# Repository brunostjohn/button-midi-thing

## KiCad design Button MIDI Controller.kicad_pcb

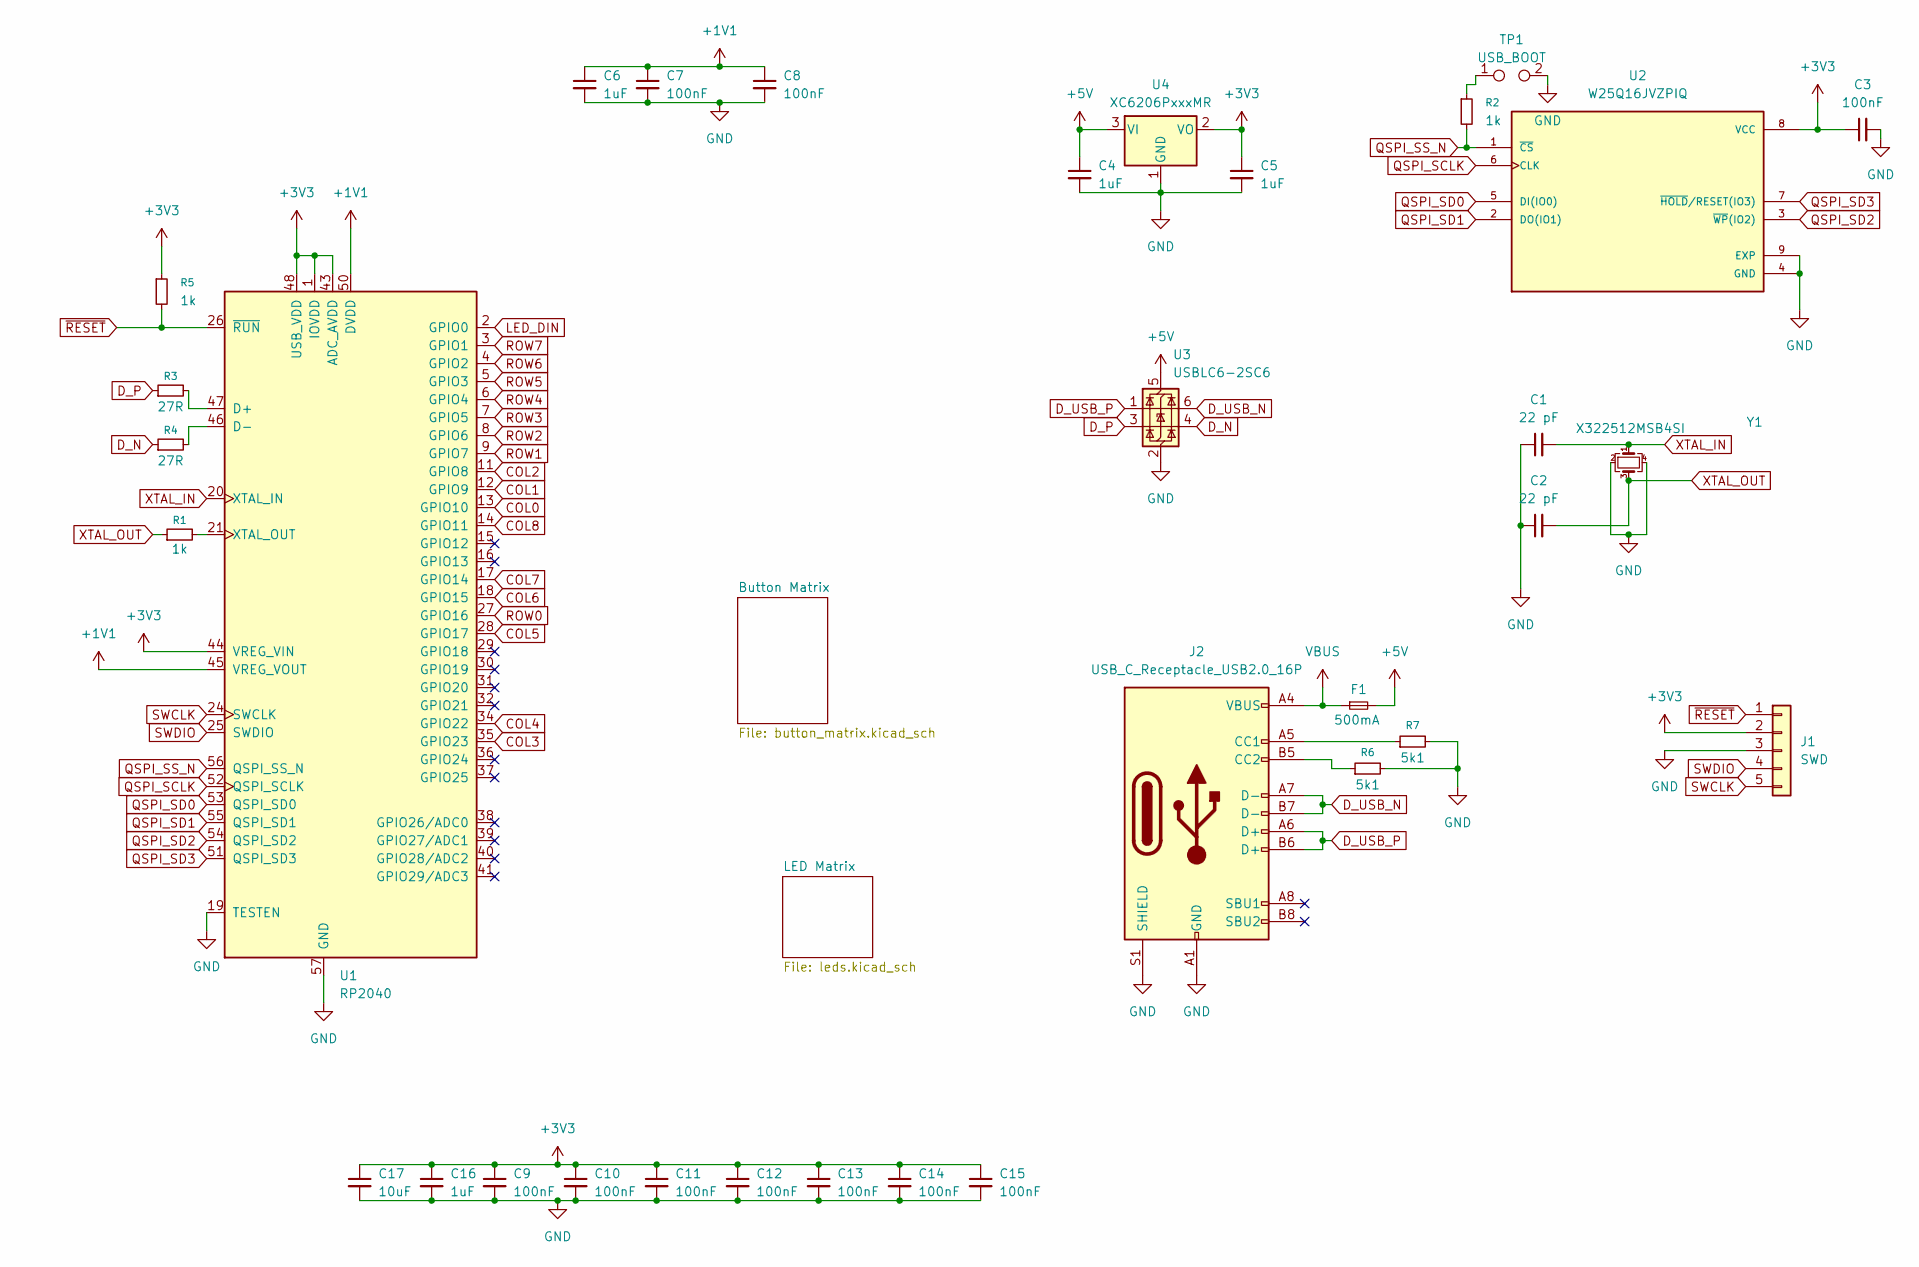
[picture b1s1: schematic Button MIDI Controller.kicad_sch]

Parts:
C1, C2: 22 pF; C_0402_1005Metric-notxt
C3, C7, C8, C9, C10, C11, C12, C13, C14, C15: 100nF; C_0402_1005Metric-notxt
C4, C5, C6, C16: 1uF; C_0402_1005Metric-notxt
C17: 10uF; C_0402_1005Metric-notxt
F1: 500mA; Fuse_0402_1005Metric-notxt
J1: SWD; PinHeader_1x05_P1.00mm_Vertical_SMD_Pin1Right-notxt
J2: USB_C_Receptacle_USB2.0_16P; USB_C_Receptacle_G-Switch_GT-USB-7025-notxt
R1, R2, R5: 1k; R_0402_1005Metric-notext
R3, R4: 27R; R_0402_1005Metric-notext
R6, R7: 5k1; R_0402_1005Metric-notext
TP1: USB_BOOT; TestPoint_Pad_1.0x1.0mm-notxt
U1: RP2040; RP2040-QFN-56-notext
U2: W25Q16JVZPIQ; SON127P500X600X80-9N-notxt
U3: USBLC6-2SC6; SOT-23-6-notxt
U4: XC6206PxxxMR; SOT-23-3-notxt
Y1: X322512MSB4SI; Crystal_SMD_2016-4Pin_2.0x1.6mm-notxt

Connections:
+1V1: C6.1, C7.1, C8.1, U1.23 (DVDD), U1.45 (VREG_VOUT), U1.50 (DVDD)
+3V3: C3.1, C5.1, C9.1, C10.1, C11.1, C12.1, C13.1, C14.1, C15.1, C16.1, C17.1, J1.2, R5.1, U1.1 (IOVDD), U1.10 (IOVDD), U1.22 (IOVDD), U1.33 (IOVDD), U1.42 (IOVDD), U1.43 (ADC_AVDD), U1.44 (VREG_VIN), U1.48 (USB_VDD), U1.49 (IOVDD), U2.8 (VCC), U4.2 (VO)
+5V: C4.1, F1.2, U3.5 (VBUS), U4.3 (VI); also elsewhere on the board
COL0: U1.13 (GPIO10); also elsewhere on the board
COL1: U1.12 (GPIO9); also elsewhere on the board
COL2: U1.11 (GPIO8); also elsewhere on the board
COL3: U1.35 (GPIO23); also elsewhere on the board
COL4: U1.34 (GPIO22); also elsewhere on the board
COL5: U1.28 (GPIO17); also elsewhere on the board
COL6: U1.18 (GPIO15); also elsewhere on the board
COL7: U1.17 (GPIO14); also elsewhere on the board
COL8: U1.14 (GPIO11); also elsewhere on the board
D_N: R4.1, U3.4 (I/O2)
D_P: R3.1, U3.3 (I/O2)
D_USB_N: J2.A7 (D-), J2.B7 (D-), U3.6 (I/O1)
D_USB_P: J2.A6 (D+), J2.B6 (D+), U3.1 (I/O1)
GND: C1.1, C2.1, C3.2, C4.2, C5.2, C6.2, C7.2, C8.2, C9.2, C10.2, C11.2, C12.2, C13.2, C14.2, C15.2, C16.2, C17.2, J1.3, J2.A1 (GND), J2.A12 (GND), J2.B1 (GND), J2.B12 (GND), J2.S1 (SHIELD), R6.2, R7.2, TP1.2, U1.19 (TESTEN), U1.57 (GND), U2.4 (GND), U2.9 (EXP), U3.2 (GND), U4.1 (GND), Y1.2, Y1.4; also elsewhere on the board
LED_DIN: U1.2 (GPIO0); also elsewhere on the board
unnamed: J2.A5 (CC1), R7.1
unnamed: J2.B5 (CC2), R6.1
unnamed: R2.1, TP1.1
unnamed: R3.2, U1.47 (D+)
unnamed: R4.2, U1.46 (D-)
unnamed: R1.2, U1.21 (XTAL_OUT)
QSPI_SCLK: U1.52 (QSPI_SCLK), U2.6 (CLK)
QSPI_SD0: U1.53 (QSPI_SD0), U2.5 (DI(IO0))
QSPI_SD1: U1.55 (QSPI_SD1), U2.2 (DO(IO1))
QSPI_SD2: U1.54 (QSPI_SD2), U2.3 (~WP(IO2))
QSPI_SD3: U1.51 (QSPI_SD3), U2.7 (~HOLD/RESET(IO3))
QSPI_SS_N: R2.2, U1.56 (QSPI_SS_N), U2.1 (~CS)
ROW0: U1.27 (GPIO16); also elsewhere on the board
ROW1: U1.9 (GPIO7); also elsewhere on the board
ROW2: U1.8 (GPIO6); also elsewhere on the board
ROW3: U1.7 (GPIO5); also elsewhere on the board
ROW4: U1.6 (GPIO4); also elsewhere on the board
ROW5: U1.5 (GPIO3); also elsewhere on the board
ROW6: U1.4 (GPIO2); also elsewhere on the board
ROW7: U1.3 (GPIO1); also elsewhere on the board
SWCLK: J1.5, U1.24 (SWCLK)
SWDIO: J1.4, U1.25 (SWDIO)
VBUS: F1.1, J2.A4 (VBUS), J2.A9 (VBUS), J2.B4 (VBUS), J2.B9 (VBUS)
XTAL_IN: C1.2, U1.20 (XTAL_IN), Y1.1
XTAL_OUT: C2.2, R1.1, Y1.3
~RESET: J1.1, R5.2, U1.26 (~RUN)

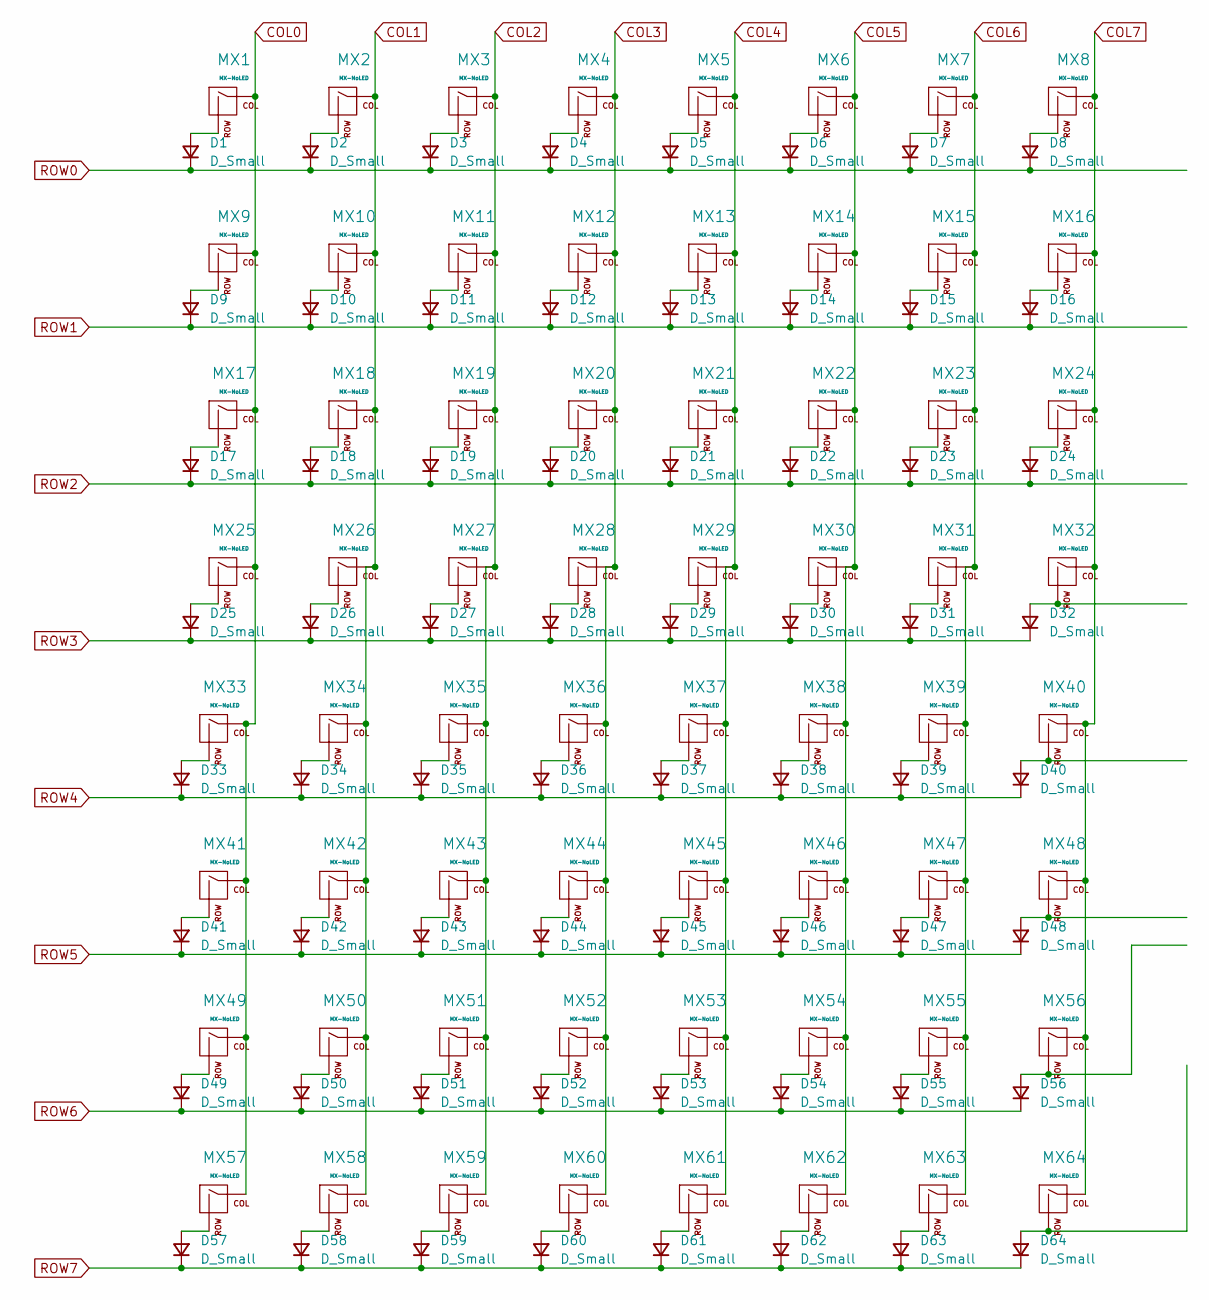
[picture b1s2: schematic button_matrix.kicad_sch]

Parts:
D1, D2, D3, D4, D5, D6, D7, D8, D9, D10, D11, D12, D13, D14, D15, D16, D17, D18, D19, D20, D21, D22, D23, D24, D25, D26, D27, D28, D29, D30, D31, D32, D33, D34, D35, D36, D37, D38, D39, D40, D41, D42, D43, D44, D45, D46, D47, D48, D49, D50, D51, D52, D53, D54, D55, D56, D57, D58, D59, D60, D61, D62, D63, D64: D_Small; D_0603_1608Metric_NOTXTNOTFUCKD
MX1, MX2, MX3, MX4, MX5, MX6, MX7, MX8, MX9, MX10, MX11, MX12, MX13, MX14, MX15, MX16, MX17, MX18, MX19, MX20, MX21, MX22, MX23, MX24, MX25, MX26, MX27, MX28, MX29, MX30, MX31, MX32, MX33, MX34, MX35, MX36, MX37, MX38, MX39, MX40, MX41, MX42, MX43, MX44, MX45, MX46, MX47, MX48, MX49, MX50, MX51, MX52, MX53, MX54, MX55, MX56, MX57, MX58, MX59, MX60, MX61, MX62, MX63, MX64: MX-NoLED; OBSC-30 SW-68

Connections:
COL0: MX1.1 (COL), MX9.1 (COL), MX17.1 (COL), MX25.1 (COL), MX33.1 (COL), MX41.1 (COL), MX49.1 (COL), MX57.1 (COL); also elsewhere on the board
COL1: MX2.1 (COL), MX10.1 (COL), MX18.1 (COL), MX26.1 (COL), MX34.1 (COL), MX42.1 (COL), MX50.1 (COL), MX58.1 (COL); also elsewhere on the board
COL2: MX3.1 (COL), MX11.1 (COL), MX19.1 (COL), MX27.1 (COL), MX35.1 (COL), MX43.1 (COL), MX51.1 (COL), MX59.1 (COL); also elsewhere on the board
COL3: MX4.1 (COL), MX12.1 (COL), MX20.1 (COL), MX28.1 (COL), MX36.1 (COL), MX44.1 (COL), MX52.1 (COL), MX60.1 (COL); also elsewhere on the board
COL4: MX5.1 (COL), MX13.1 (COL), MX21.1 (COL), MX29.1 (COL), MX37.1 (COL), MX45.1 (COL), MX53.1 (COL), MX61.1 (COL); also elsewhere on the board
COL5: MX6.1 (COL), MX14.1 (COL), MX22.1 (COL), MX30.1 (COL), MX38.1 (COL), MX46.1 (COL), MX54.1 (COL), MX62.1 (COL); also elsewhere on the board
COL6: MX7.1 (COL), MX15.1 (COL), MX23.1 (COL), MX31.1 (COL), MX39.1 (COL), MX47.1 (COL), MX55.1 (COL), MX63.1 (COL); also elsewhere on the board
COL7: MX8.1 (COL), MX16.1 (COL), MX24.1 (COL), MX32.1 (COL), MX40.1 (COL), MX48.1 (COL), MX56.1 (COL), MX64.1 (COL); also elsewhere on the board
unnamed: D1.2 (A), MX1.2 (ROW)
unnamed: D2.2 (A), MX2.2 (ROW)
unnamed: D3.2 (A), MX3.2 (ROW)
unnamed: D4.2 (A), MX4.2 (ROW)
unnamed: D5.2 (A), MX5.2 (ROW)
unnamed: D6.2 (A), MX6.2 (ROW)
unnamed: D7.2 (A), MX7.2 (ROW)
unnamed: D8.2 (A), MX8.2 (ROW)
unnamed: D9.2 (A), MX9.2 (ROW)
unnamed: D10.2 (A), MX10.2 (ROW)
unnamed: D11.2 (A), MX11.2 (ROW)
unnamed: D12.2 (A), MX12.2 (ROW)
unnamed: D13.2 (A), MX13.2 (ROW)
unnamed: D14.2 (A), MX14.2 (ROW)
unnamed: D15.2 (A), MX15.2 (ROW)
unnamed: D16.2 (A), MX16.2 (ROW)
unnamed: D17.2 (A), MX17.2 (ROW)
unnamed: D18.2 (A), MX18.2 (ROW)
unnamed: D19.2 (A), MX19.2 (ROW)
unnamed: D20.2 (A), MX20.2 (ROW)
unnamed: D21.2 (A), MX21.2 (ROW)
unnamed: D22.2 (A), MX22.2 (ROW)
unnamed: D23.2 (A), MX23.2 (ROW)
unnamed: D24.2 (A), MX24.2 (ROW)
unnamed: D25.2 (A), MX25.2 (ROW)
unnamed: D26.2 (A), MX26.2 (ROW)
unnamed: D27.2 (A), MX27.2 (ROW)
unnamed: D28.2 (A), MX28.2 (ROW)
unnamed: D29.2 (A), MX29.2 (ROW)
unnamed: D30.2 (A), MX30.2 (ROW)
unnamed: D31.2 (A), MX31.2 (ROW)
unnamed: D32.2 (A), MX32.2 (ROW)
unnamed: D33.2 (A), MX33.2 (ROW)
unnamed: D34.2 (A), MX34.2 (ROW)
unnamed: D35.2 (A), MX35.2 (ROW)
unnamed: D36.2 (A), MX36.2 (ROW)
unnamed: D37.2 (A), MX37.2 (ROW)
unnamed: D38.2 (A), MX38.2 (ROW)
unnamed: D39.2 (A), MX39.2 (ROW)
unnamed: D40.2 (A), MX40.2 (ROW)
unnamed: D41.2 (A), MX41.2 (ROW)
unnamed: D42.2 (A), MX42.2 (ROW)
unnamed: D43.2 (A), MX43.2 (ROW)
unnamed: D44.2 (A), MX44.2 (ROW)
unnamed: D45.2 (A), MX45.2 (ROW)
unnamed: D46.2 (A), MX46.2 (ROW)
unnamed: D47.2 (A), MX47.2 (ROW)
unnamed: D48.2 (A), MX48.2 (ROW)
unnamed: D49.2 (A), MX49.2 (ROW)
unnamed: D50.2 (A), MX50.2 (ROW)
unnamed: D51.2 (A), MX51.2 (ROW)
unnamed: D52.2 (A), MX52.2 (ROW)
unnamed: D53.2 (A), MX53.2 (ROW)
unnamed: D54.2 (A), MX54.2 (ROW)
unnamed: D55.2 (A), MX55.2 (ROW)
unnamed: D56.2 (A), MX56.2 (ROW)
unnamed: D57.2 (A), MX57.2 (ROW)
unnamed: D58.2 (A), MX58.2 (ROW)
unnamed: D59.2 (A), MX59.2 (ROW)
unnamed: D60.2 (A), MX60.2 (ROW)
unnamed: D61.2 (A), MX61.2 (ROW)
unnamed: D62.2 (A), MX62.2 (ROW)
unnamed: D63.2 (A), MX63.2 (ROW)
unnamed: D64.2 (A), MX64.2 (ROW)
ROW0: D1.1 (K), D2.1 (K), D3.1 (K), D4.1 (K), D5.1 (K), D6.1 (K), D7.1 (K), D8.1 (K); also elsewhere on the board
ROW1: D9.1 (K), D10.1 (K), D11.1 (K), D12.1 (K), D13.1 (K), D14.1 (K), D15.1 (K), D16.1 (K); also elsewhere on the board
ROW2: D17.1 (K), D18.1 (K), D19.1 (K), D20.1 (K), D21.1 (K), D22.1 (K), D23.1 (K), D24.1 (K); also elsewhere on the board
ROW3: D25.1 (K), D26.1 (K), D27.1 (K), D28.1 (K), D29.1 (K), D30.1 (K), D31.1 (K), D32.1 (K); also elsewhere on the board
ROW4: D33.1 (K), D34.1 (K), D35.1 (K), D36.1 (K), D37.1 (K), D38.1 (K), D39.1 (K), D40.1 (K); also elsewhere on the board
ROW5: D41.1 (K), D42.1 (K), D43.1 (K), D44.1 (K), D45.1 (K), D46.1 (K), D47.1 (K), D48.1 (K); also elsewhere on the board
ROW6: D49.1 (K), D50.1 (K), D51.1 (K), D52.1 (K), D53.1 (K), D54.1 (K), D55.1 (K), D56.1 (K); also elsewhere on the board
ROW7: D57.1 (K), D58.1 (K), D59.1 (K), D60.1 (K), D61.1 (K), D62.1 (K), D63.1 (K), D64.1 (K); also elsewhere on the board

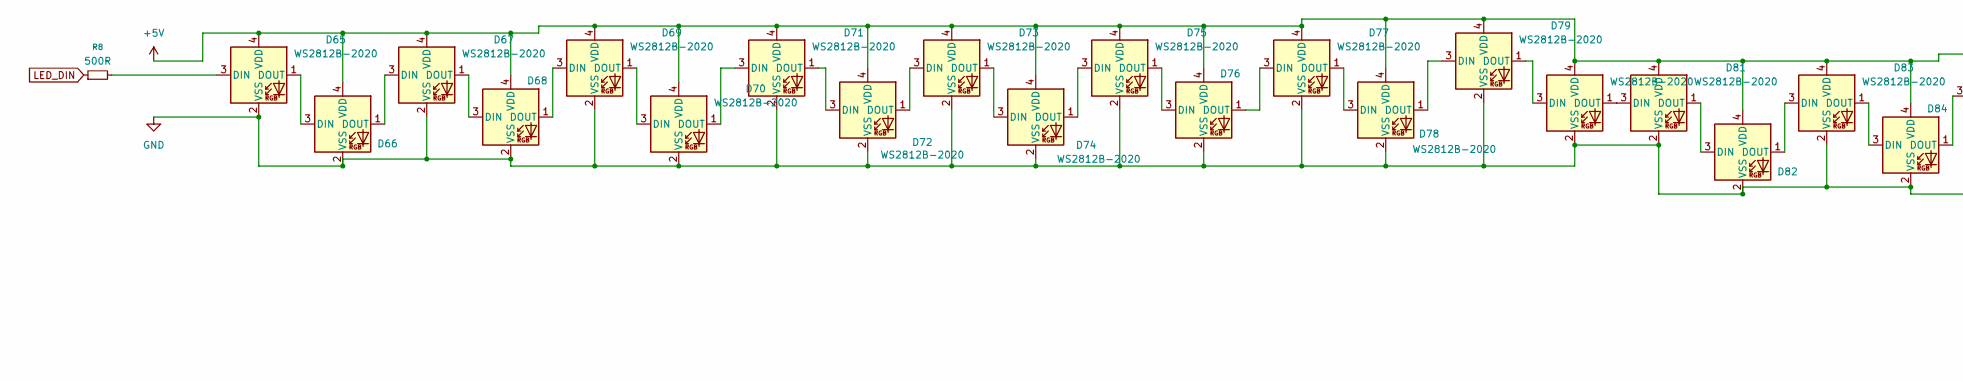
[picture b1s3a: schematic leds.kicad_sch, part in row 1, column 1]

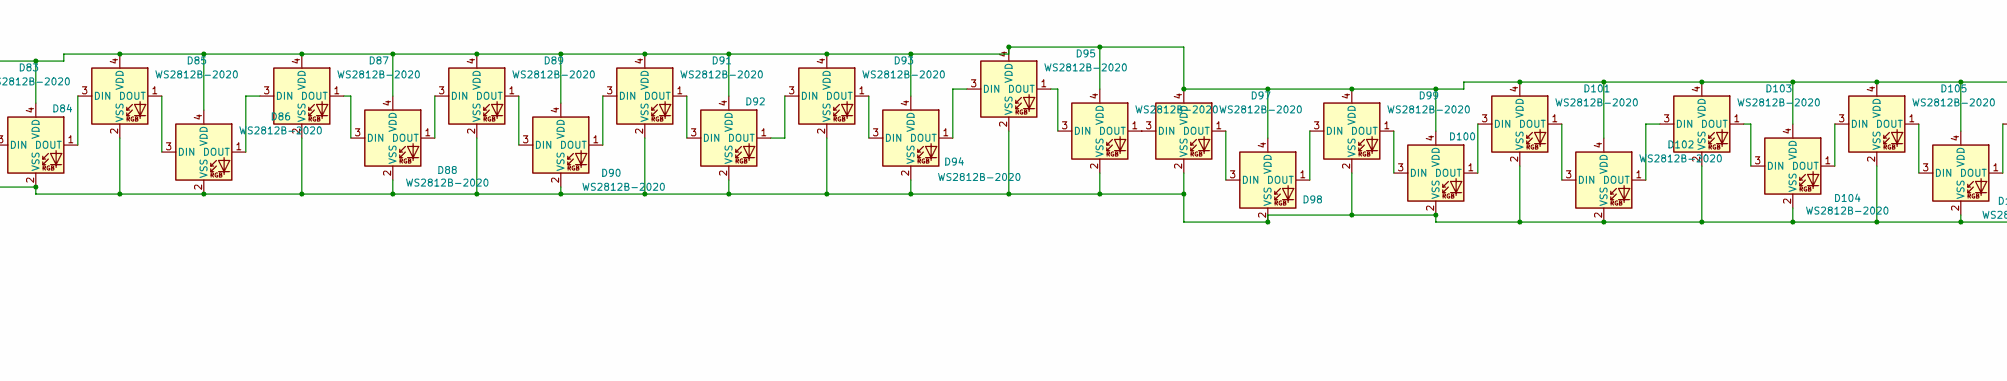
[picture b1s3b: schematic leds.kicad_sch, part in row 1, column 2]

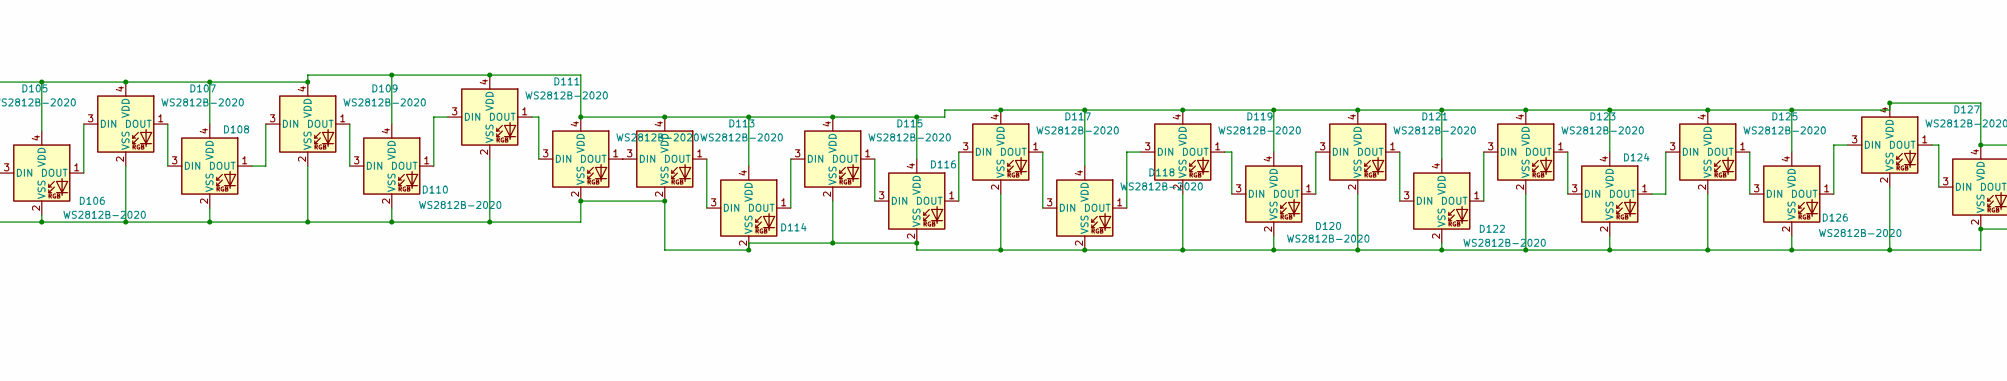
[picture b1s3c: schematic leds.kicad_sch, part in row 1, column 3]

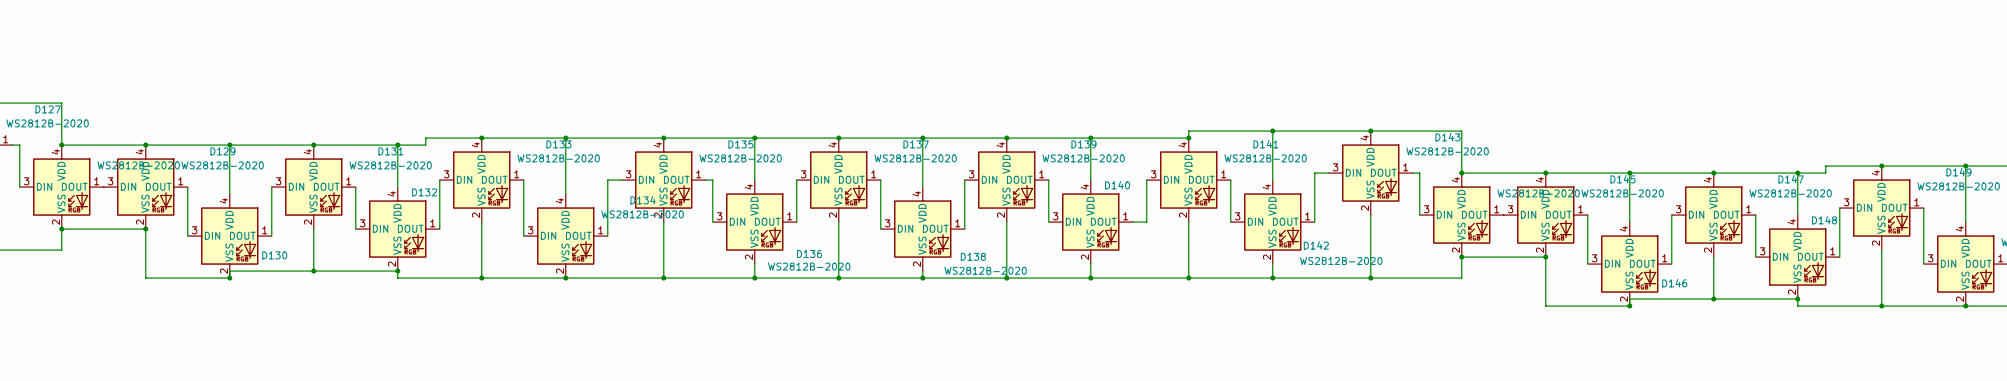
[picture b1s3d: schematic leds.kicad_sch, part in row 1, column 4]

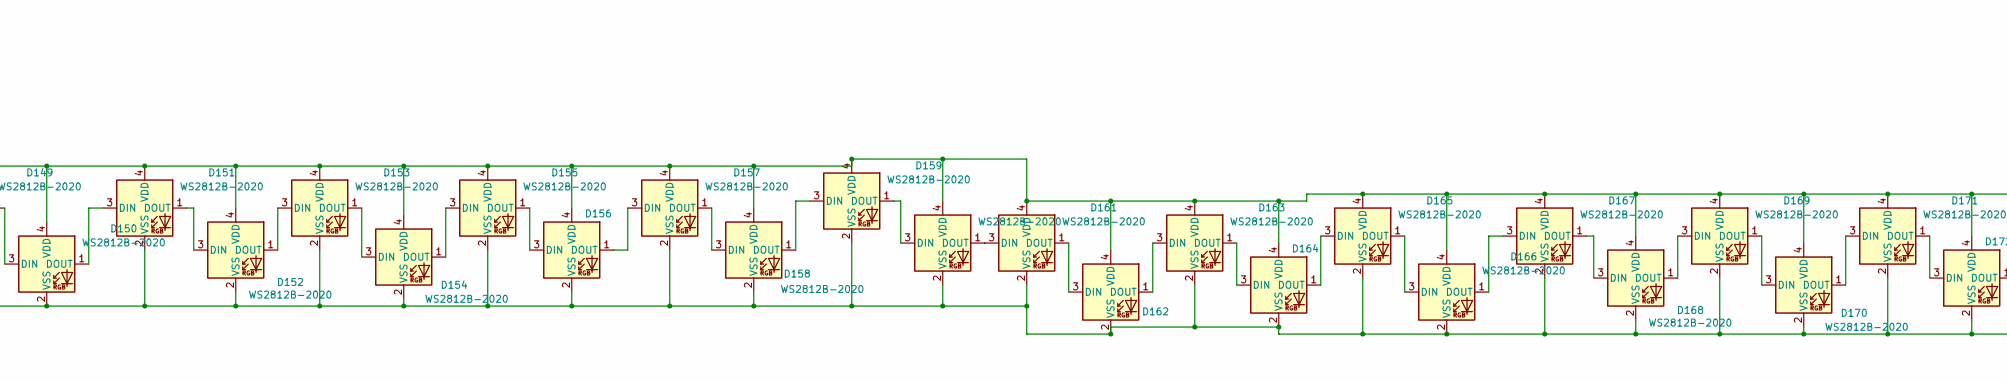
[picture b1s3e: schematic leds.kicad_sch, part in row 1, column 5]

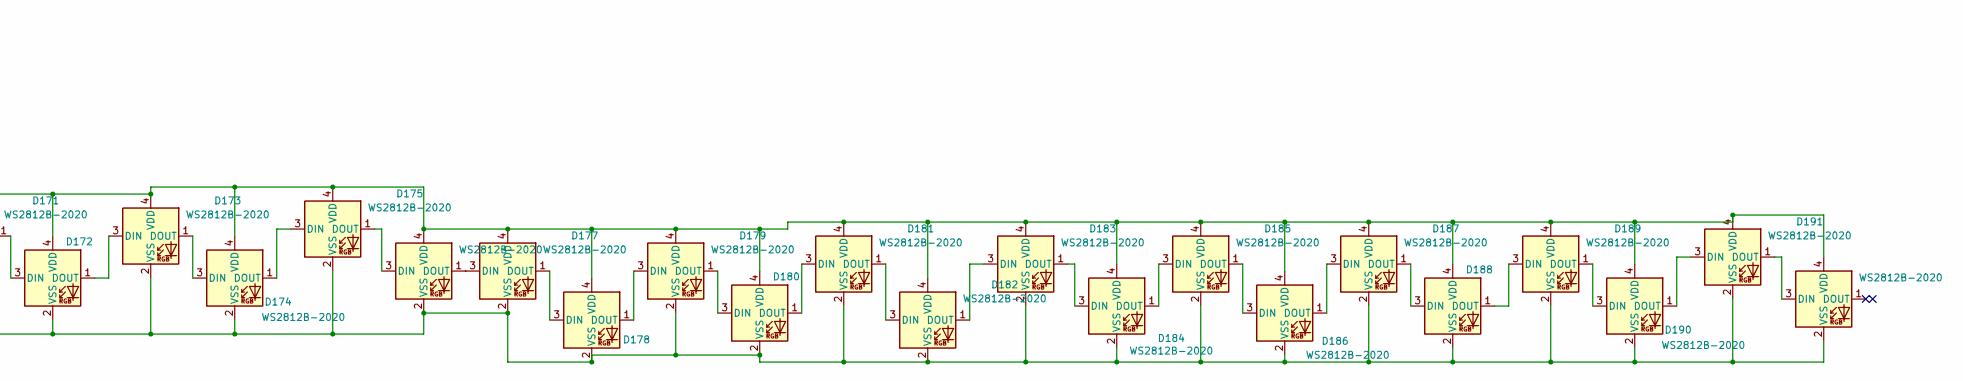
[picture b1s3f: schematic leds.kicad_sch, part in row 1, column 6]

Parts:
D65, D66, D67, D68, D69, D70, D71, D72, D73, D74, D75, D76, D77, D78, D79, D80, D81, D82, D83, D84, D85, D86, D87, D88, D89, D90, D91, D92, D93, D94, D95, D96, D97, D98, D99, D100, D101, D102, D103, D104, D105, D106, D107, D108, D109, D110, D111, D112, D113, D114, D115, D116, D117, D118, D119, D120, D121, D122, D123, D124, D125, D126, D127, D128, D129, D130, D131, D132, D133, D134, D135, D136, D137, D138, D139, D140, D141, D142, D143, D144, D145, D146, D147, D148, D149, D150, D151, D152, D153, D154, D155, D156, D157, D158, D159, D160, D161, D162, D163, D164, D165, D166, D167, D168, D169, D170, D171, D172, D173, D174, D175, D176, D177, D178, D179, D180, D181, D182, D183, D184, D185, D186, D187, D188, D189, D190, D191, D192: WS2812B-2020; LED_WS2812B-2020_PLCC4_2.0x2.0mm-notext
R8: 500R; R_0402_1005Metric-notext

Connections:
+5V: D65.4 (VDD), D66.4 (VDD), D67.4 (VDD), D68.4 (VDD), D69.4 (VDD), D70.4 (VDD), D71.4 (VDD), D72.4 (VDD), D73.4 (VDD), D74.4 (VDD), D75.4 (VDD), D76.4 (VDD), D77.4 (VDD), D78.4 (VDD), D79.4 (VDD), D80.4 (VDD), D81.4 (VDD), D82.4 (VDD), D83.4 (VDD), D84.4 (VDD), D85.4 (VDD), D86.4 (VDD), D87.4 (VDD), D88.4 (VDD), D89.4 (VDD), D90.4 (VDD), D91.4 (VDD), D92.4 (VDD), D93.4 (VDD), D94.4 (VDD), D95.4 (VDD), D96.4 (VDD), D97.4 (VDD), D98.4 (VDD), D99.4 (VDD), D100.4 (VDD), D101.4 (VDD), D102.4 (VDD), D103.4 (VDD), D104.4 (VDD), D105.4 (VDD), D106.4 (VDD), D107.4 (VDD), D108.4 (VDD), D109.4 (VDD), D110.4 (VDD), D111.4 (VDD), D112.4 (VDD), D113.4 (VDD), D114.4 (VDD), D115.4 (VDD), D116.4 (VDD), D117.4 (VDD), D118.4 (VDD), D119.4 (VDD), D120.4 (VDD), D121.4 (VDD), D122.4 (VDD), D123.4 (VDD), D124.4 (VDD), D125.4 (VDD), D126.4 (VDD), D127.4 (VDD), D128.4 (VDD), D129.4 (VDD), D130.4 (VDD), D131.4 (VDD), D132.4 (VDD), D133.4 (VDD), D134.4 (VDD), D135.4 (VDD), D136.4 (VDD), D137.4 (VDD), D138.4 (VDD), D139.4 (VDD), D140.4 (VDD), D141.4 (VDD), D142.4 (VDD), D143.4 (VDD), D144.4 (VDD), D145.4 (VDD), D146.4 (VDD), D147.4 (VDD), D148.4 (VDD), D149.4 (VDD), D150.4 (VDD), D151.4 (VDD), D152.4 (VDD), D153.4 (VDD), D154.4 (VDD), D155.4 (VDD), D156.4 (VDD), D157.4 (VDD), D158.4 (VDD), D159.4 (VDD), D160.4 (VDD), D161.4 (VDD), D162.4 (VDD), D163.4 (VDD), D164.4 (VDD), D165.4 (VDD), D166.4 (VDD), D167.4 (VDD), D168.4 (VDD), D169.4 (VDD), D170.4 (VDD), D171.4 (VDD), D172.4 (VDD), D173.4 (VDD), D174.4 (VDD), D175.4 (VDD), D176.4 (VDD), D177.4 (VDD), D178.4 (VDD), D179.4 (VDD), D180.4 (VDD), D181.4 (VDD), D182.4 (VDD), D183.4 (VDD), D184.4 (VDD), D185.4 (VDD), D186.4 (VDD), D187.4 (VDD), D188.4 (VDD), D189.4 (VDD), D190.4 (VDD), D191.4 (VDD), D192.4 (VDD); also elsewhere on the board
GND: D65.2 (VSS), D66.2 (VSS), D67.2 (VSS), D68.2 (VSS), D69.2 (VSS), D70.2 (VSS), D71.2 (VSS), D72.2 (VSS), D73.2 (VSS), D74.2 (VSS), D75.2 (VSS), D76.2 (VSS), D77.2 (VSS), D78.2 (VSS), D79.2 (VSS), D80.2 (VSS), D81.2 (VSS), D82.2 (VSS), D83.2 (VSS), D84.2 (VSS), D85.2 (VSS), D86.2 (VSS), D87.2 (VSS), D88.2 (VSS), D89.2 (VSS), D90.2 (VSS), D91.2 (VSS), D92.2 (VSS), D93.2 (VSS), D94.2 (VSS), D95.2 (VSS), D96.2 (VSS), D97.2 (VSS), D98.2 (VSS), D99.2 (VSS), D100.2 (VSS), D101.2 (VSS), D102.2 (VSS), D103.2 (VSS), D104.2 (VSS), D105.2 (VSS), D106.2 (VSS), D107.2 (VSS), D108.2 (VSS), D109.2 (VSS), D110.2 (VSS), D111.2 (VSS), D112.2 (VSS), D113.2 (VSS), D114.2 (VSS), D115.2 (VSS), D116.2 (VSS), D117.2 (VSS), D118.2 (VSS), D119.2 (VSS), D120.2 (VSS), D121.2 (VSS), D122.2 (VSS), D123.2 (VSS), D124.2 (VSS), D125.2 (VSS), D126.2 (VSS), D127.2 (VSS), D128.2 (VSS), D129.2 (VSS), D130.2 (VSS), D131.2 (VSS), D132.2 (VSS), D133.2 (VSS), D134.2 (VSS), D135.2 (VSS), D136.2 (VSS), D137.2 (VSS), D138.2 (VSS), D139.2 (VSS), D140.2 (VSS), D141.2 (VSS), D142.2 (VSS), D143.2 (VSS), D144.2 (VSS), D145.2 (VSS), D146.2 (VSS), D147.2 (VSS), D148.2 (VSS), D149.2 (VSS), D150.2 (VSS), D151.2 (VSS), D152.2 (VSS), D153.2 (VSS), D154.2 (VSS), D155.2 (VSS), D156.2 (VSS), D157.2 (VSS), D158.2 (VSS), D159.2 (VSS), D160.2 (VSS), D161.2 (VSS), D162.2 (VSS), D163.2 (VSS), D164.2 (VSS), D165.2 (VSS), D166.2 (VSS), D167.2 (VSS), D168.2 (VSS), D169.2 (VSS), D170.2 (VSS), D171.2 (VSS), D172.2 (VSS), D173.2 (VSS), D174.2 (VSS), D175.2 (VSS), D176.2 (VSS), D177.2 (VSS), D178.2 (VSS), D179.2 (VSS), D180.2 (VSS), D181.2 (VSS), D182.2 (VSS), D183.2 (VSS), D184.2 (VSS), D185.2 (VSS), D186.2 (VSS), D187.2 (VSS), D188.2 (VSS), D189.2 (VSS), D190.2 (VSS), D191.2 (VSS), D192.2 (VSS); also elsewhere on the board
LED_DIN: R8.1; also elsewhere on the board
unnamed: D65.3 (DIN), R8.2
unnamed: D65.1 (DOUT), D66.3 (DIN)
unnamed: D66.1 (DOUT), D67.3 (DIN)
unnamed: D67.1 (DOUT), D68.3 (DIN)
unnamed: D68.1 (DOUT), D69.3 (DIN)
unnamed: D69.1 (DOUT), D70.3 (DIN)
unnamed: D70.1 (DOUT), D71.3 (DIN)
unnamed: D71.1 (DOUT), D72.3 (DIN)
unnamed: D72.1 (DOUT), D73.3 (DIN)
unnamed: D73.1 (DOUT), D74.3 (DIN)
unnamed: D74.1 (DOUT), D75.3 (DIN)
unnamed: D75.1 (DOUT), D76.3 (DIN)
unnamed: D76.1 (DOUT), D77.3 (DIN)
unnamed: D77.1 (DOUT), D78.3 (DIN)
unnamed: D78.1 (DOUT), D79.3 (DIN)
unnamed: D79.1 (DOUT), D80.3 (DIN)
unnamed: D80.1 (DOUT), D81.3 (DIN)
unnamed: D81.1 (DOUT), D82.3 (DIN)
unnamed: D82.1 (DOUT), D83.3 (DIN)
unnamed: D83.1 (DOUT), D84.3 (DIN)
unnamed: D84.1 (DOUT), D85.3 (DIN)
unnamed: D85.1 (DOUT), D86.3 (DIN)
unnamed: D86.1 (DOUT), D87.3 (DIN)
unnamed: D87.1 (DOUT), D88.3 (DIN)
unnamed: D88.1 (DOUT), D89.3 (DIN)
unnamed: D89.1 (DOUT), D90.3 (DIN)
unnamed: D90.1 (DOUT), D91.3 (DIN)
unnamed: D91.1 (DOUT), D92.3 (DIN)
unnamed: D92.1 (DOUT), D93.3 (DIN)
unnamed: D93.1 (DOUT), D94.3 (DIN)
unnamed: D94.1 (DOUT), D95.3 (DIN)
unnamed: D95.1 (DOUT), D96.3 (DIN)
unnamed: D96.1 (DOUT), D97.3 (DIN)
unnamed: D97.1 (DOUT), D98.3 (DIN)
unnamed: D98.1 (DOUT), D99.3 (DIN)
unnamed: D99.1 (DOUT), D100.3 (DIN)
unnamed: D100.1 (DOUT), D101.3 (DIN)
unnamed: D101.1 (DOUT), D102.3 (DIN)
unnamed: D102.1 (DOUT), D103.3 (DIN)
unnamed: D103.1 (DOUT), D104.3 (DIN)
unnamed: D104.1 (DOUT), D105.3 (DIN)
unnamed: D105.1 (DOUT), D106.3 (DIN)
unnamed: D106.1 (DOUT), D107.3 (DIN)
unnamed: D107.1 (DOUT), D108.3 (DIN)
unnamed: D108.1 (DOUT), D109.3 (DIN)
unnamed: D109.1 (DOUT), D110.3 (DIN)
unnamed: D110.1 (DOUT), D111.3 (DIN)
unnamed: D111.1 (DOUT), D112.3 (DIN)
unnamed: D112.1 (DOUT), D113.3 (DIN)
unnamed: D113.1 (DOUT), D114.3 (DIN)
unnamed: D114.1 (DOUT), D115.3 (DIN)
unnamed: D115.1 (DOUT), D116.3 (DIN)
unnamed: D116.1 (DOUT), D117.3 (DIN)
unnamed: D117.1 (DOUT), D118.3 (DIN)
unnamed: D118.1 (DOUT), D119.3 (DIN)
unnamed: D119.1 (DOUT), D120.3 (DIN)
unnamed: D120.1 (DOUT), D121.3 (DIN)
unnamed: D121.1 (DOUT), D122.3 (DIN)
unnamed: D122.1 (DOUT), D123.3 (DIN)
unnamed: D123.1 (DOUT), D124.3 (DIN)
unnamed: D124.1 (DOUT), D125.3 (DIN)
unnamed: D125.1 (DOUT), D126.3 (DIN)
unnamed: D126.1 (DOUT), D127.3 (DIN)
unnamed: D127.1 (DOUT), D128.3 (DIN)
unnamed: D128.1 (DOUT), D129.3 (DIN)
unnamed: D129.1 (DOUT), D130.3 (DIN)
unnamed: D130.1 (DOUT), D131.3 (DIN)
unnamed: D131.1 (DOUT), D132.3 (DIN)
unnamed: D132.1 (DOUT), D133.3 (DIN)
unnamed: D133.1 (DOUT), D134.3 (DIN)
unnamed: D134.1 (DOUT), D135.3 (DIN)
unnamed: D135.1 (DOUT), D136.3 (DIN)
unnamed: D136.1 (DOUT), D137.3 (DIN)
unnamed: D137.1 (DOUT), D138.3 (DIN)
unnamed: D138.1 (DOUT), D139.3 (DIN)
unnamed: D139.1 (DOUT), D140.3 (DIN)
unnamed: D140.1 (DOUT), D141.3 (DIN)
unnamed: D141.1 (DOUT), D142.3 (DIN)
unnamed: D142.1 (DOUT), D143.3 (DIN)
unnamed: D143.1 (DOUT), D144.3 (DIN)
unnamed: D144.1 (DOUT), D145.3 (DIN)
unnamed: D145.1 (DOUT), D146.3 (DIN)
unnamed: D146.1 (DOUT), D147.3 (DIN)
unnamed: D147.1 (DOUT), D148.3 (DIN)
unnamed: D148.1 (DOUT), D149.3 (DIN)
unnamed: D149.1 (DOUT), D150.3 (DIN)
unnamed: D150.1 (DOUT), D151.3 (DIN)
unnamed: D151.1 (DOUT), D152.3 (DIN)
unnamed: D152.1 (DOUT), D153.3 (DIN)
unnamed: D153.1 (DOUT), D154.3 (DIN)
unnamed: D154.1 (DOUT), D155.3 (DIN)
unnamed: D155.1 (DOUT), D156.3 (DIN)
unnamed: D156.1 (DOUT), D157.3 (DIN)
unnamed: D157.1 (DOUT), D158.3 (DIN)
unnamed: D158.1 (DOUT), D159.3 (DIN)
unnamed: D159.1 (DOUT), D160.3 (DIN)
unnamed: D160.1 (DOUT), D161.3 (DIN)
unnamed: D161.1 (DOUT), D162.3 (DIN)
unnamed: D162.1 (DOUT), D163.3 (DIN)
unnamed: D163.1 (DOUT), D164.3 (DIN)
unnamed: D164.1 (DOUT), D165.3 (DIN)
unnamed: D165.1 (DOUT), D166.3 (DIN)
unnamed: D166.1 (DOUT), D167.3 (DIN)
unnamed: D167.1 (DOUT), D168.3 (DIN)
unnamed: D168.1 (DOUT), D169.3 (DIN)
unnamed: D169.1 (DOUT), D170.3 (DIN)
unnamed: D170.1 (DOUT), D171.3 (DIN)
unnamed: D171.1 (DOUT), D172.3 (DIN)
unnamed: D172.1 (DOUT), D173.3 (DIN)
unnamed: D173.1 (DOUT), D174.3 (DIN)
unnamed: D174.1 (DOUT), D175.3 (DIN)
unnamed: D175.1 (DOUT), D176.3 (DIN)
unnamed: D176.1 (DOUT), D177.3 (DIN)
unnamed: D177.1 (DOUT), D178.3 (DIN)
unnamed: D178.1 (DOUT), D179.3 (DIN)
unnamed: D179.1 (DOUT), D180.3 (DIN)
unnamed: D180.1 (DOUT), D181.3 (DIN)
unnamed: D181.1 (DOUT), D182.3 (DIN)
unnamed: D182.1 (DOUT), D183.3 (DIN)
unnamed: D183.1 (DOUT), D184.3 (DIN)
unnamed: D184.1 (DOUT), D185.3 (DIN)
unnamed: D185.1 (DOUT), D186.3 (DIN)
unnamed: D186.1 (DOUT), D187.3 (DIN)
unnamed: D187.1 (DOUT), D188.3 (DIN)
unnamed: D188.1 (DOUT), D189.3 (DIN)
unnamed: D189.1 (DOUT), D190.3 (DIN)
unnamed: D190.1 (DOUT), D191.3 (DIN)
unnamed: D191.1 (DOUT), D192.3 (DIN)
